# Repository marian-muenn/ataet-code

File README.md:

# Dokumentation des Projektes

## Projektrstruktur

- `./src`
  - beinhaltet den Quellcode
- `./boards`
  - beinhaltet die Devicetree overlays
- `./prj.conf`
  - beinhaltet die Kernel-Konfiguration
- `./doc`
  - beinhaltet die Dokumtation des C Codes
- `./west`
  - beinhaltet Metadaten für das Build Tool
- `./kicad`
  - beinhaltet das Kicad-Projekt zur Platine

## Installation der benötigten Tool

Zur Installation der Tools unter Linux liegen 3 Skripte bei,
die sukzessive ausgeführt werden müssen.

- `./install-zephyr-sdk.sh`
  - Installiert das Zephyr SDK
- `./create-venv.sh`
  - Richtet eine virtuelle Python Umgebung mit dem von Zephyr
  genutzten build Tool "west" ein
- `./west_init.sh`
  - Initialisiert den West workspace

Alternativ kann auch der
  [offizielle Installationsguide](https://docs.zephyrproject.org/latest/develop/getting_started/index.html)
  genutzt werden.

- Außerdem werden Cmake, Python und Python-venv benötigt.

## Eintragen der Passwörter

- Aus Sicherheitsgründen sind die Benutzerpasswörter für MQTT entfernt worden.
- Diese müssen in den Dateien src/mm_config.h und mqtt-py/mqtt.py eintgetragen werden.

## Kompilieren und installieren der Firmware

- Das STM Nucleo-F756zg entwicklunsboard muss mit dem PC über USB erbunden werden.
- Mit `source .venv/bin/activate` wird die Python Umgebung mit den build tools eingebunden.
- Mit `west build -b nucleo_f756zg -p` wird der Programmcode für ein Board mit LTE-Modem kompiliert
- Mit `west build -b nucleo_f756zg -p -D -- -DOVERLAY_CONF=wifi.conf` wird der Programmcode für die Platine mit WLAN Modul kompiliert
- Anschließend kann das Programm mit `west flash` auf den
  Microcontroller übertragen werden

## Konsolenlog und Debugging

- mit `picocom /dev/ttyACM0 --baud=115200` wird der Konsolenoutput des
  Microcontrollers angezeigt.
- Mit `west debug` kann außerdem eine gdb Sitzung zum Debugging gestartet werden.

## Empfangen der Fotos über MQTT

- In mqtt-py liegt ein kleines Python tool, das es ermöglicht die Bilder
  über den MQTT Sever zu empfangen.
- Dieses lässt sich mit `python mqtt-py/mqtt.py` ausführen.
- Anschließend meldet sich das Tool am MQTT-Server an und speichert das
  neuste .jpeg in den lokalen ordner.

## Erstellen der Codedokumentation

- Mit dem tool `doxygen` kann die Dokumentation erstellt werden
- Diese liegt dann im Verzeichnis ./doc in den Dateiformaten .html und als Latex-Dokument

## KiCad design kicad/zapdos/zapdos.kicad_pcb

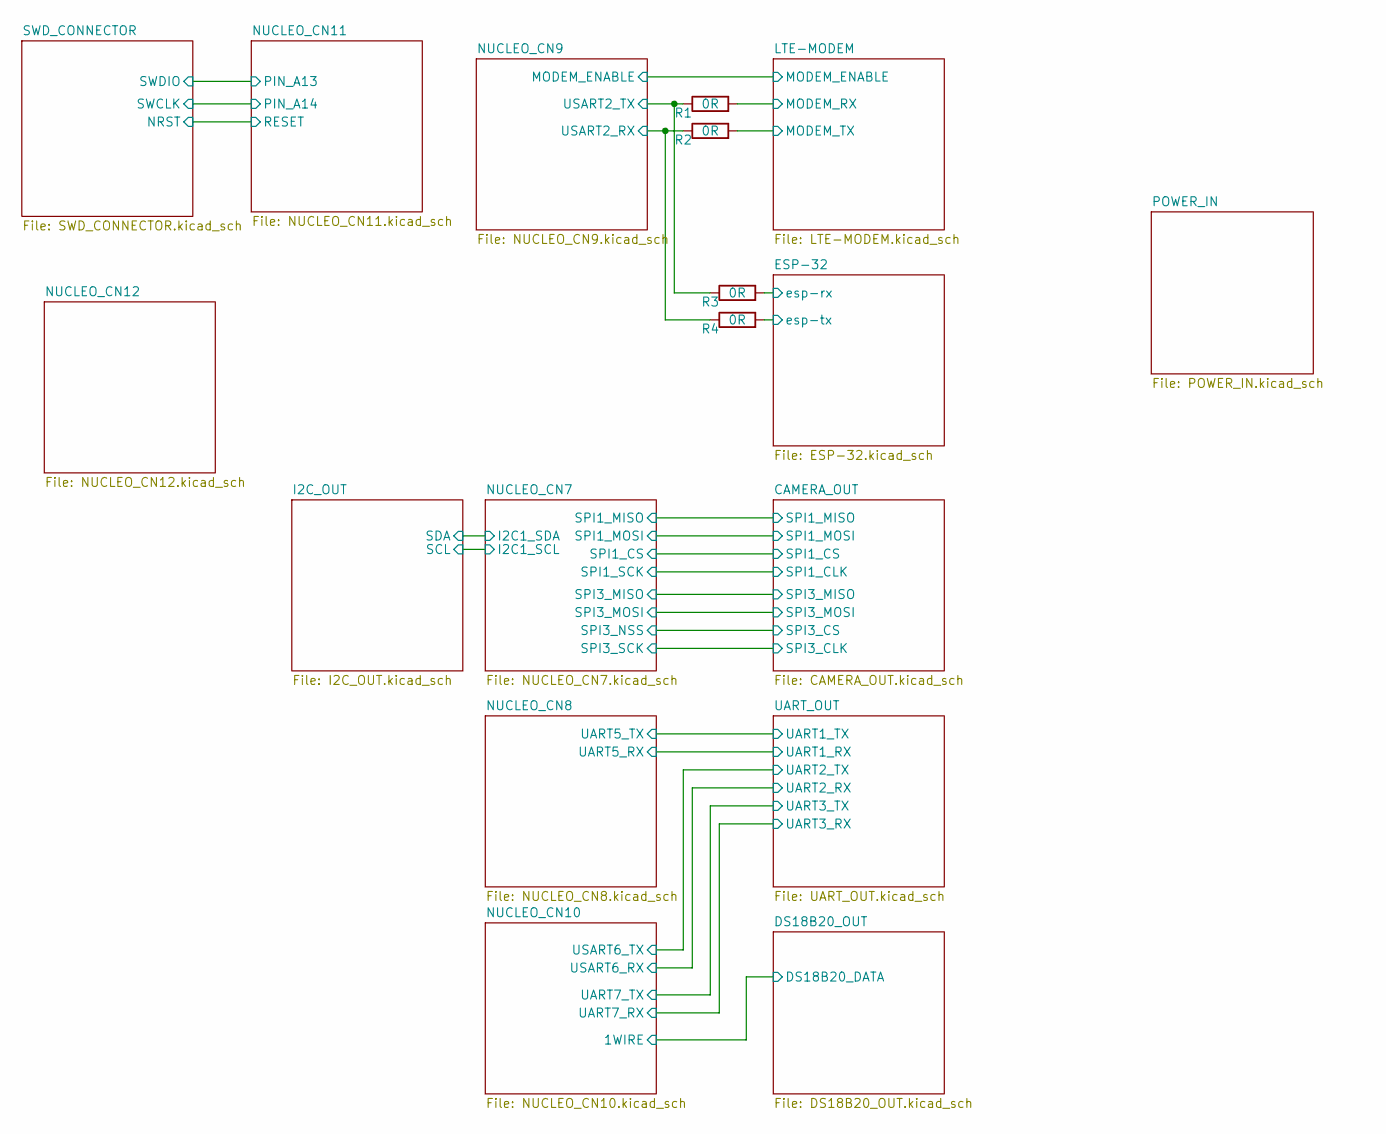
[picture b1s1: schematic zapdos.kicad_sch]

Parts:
R1, R2, R3, R4: 0R; R_0805_2012Metric_Pad1.20x1.40mm_HandSolder

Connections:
/ESP-32/esp-rx: R3.2; also elsewhere on the board
/ESP-32/esp-tx: R4.2; also elsewhere on the board
/LTE-MODEM/MODEM_RX: R1.2; also elsewhere on the board
/LTE-MODEM/MODEM_TX: R2.2; also elsewhere on the board
/NUCLEO_CN9/USART2_RX: R2.1, R4.1; also elsewhere on the board
/NUCLEO_CN9/USART2_TX: R1.1, R3.1; also elsewhere on the board

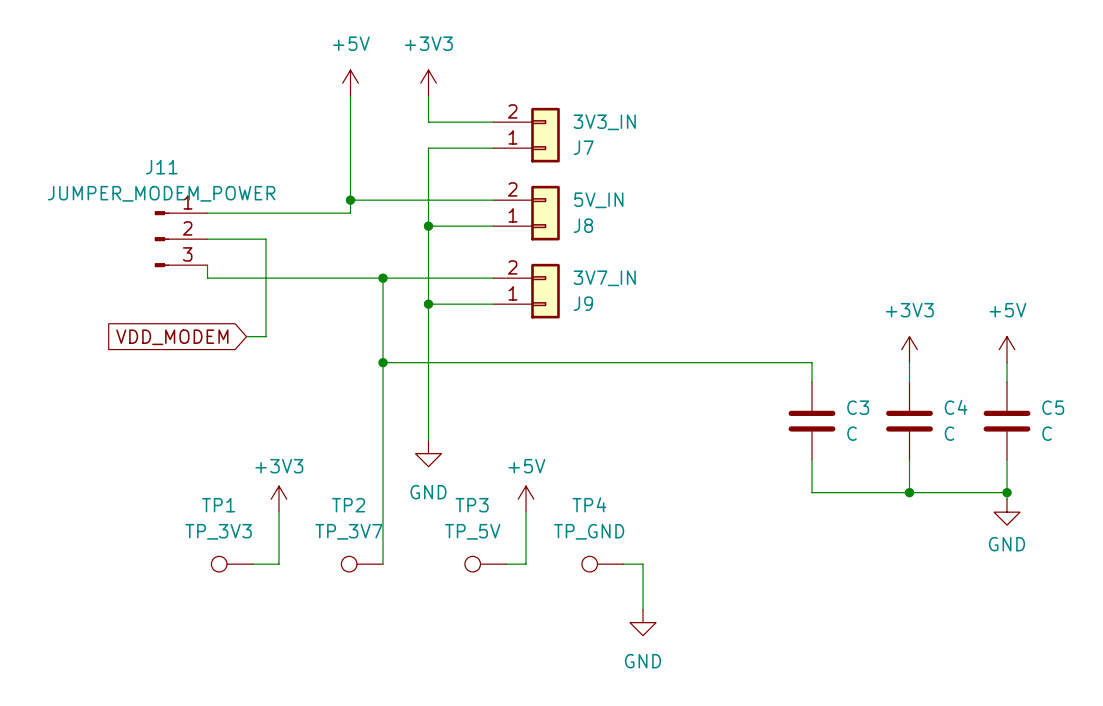
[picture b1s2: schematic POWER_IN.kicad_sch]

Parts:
C3, C4, C5: C; C_1210_3225Metric_Pad1.33x2.70mm_HandSolder
J7: 3V3_IN; JST_PH_B2B-PH-K_1x02_P2.00mm_Vertical
J8: 5V_IN; JST_PH_B2B-PH-K_1x02_P2.00mm_Vertical
J9: 3V7_IN; JST_PH_B2B-PH-K_1x02_P2.00mm_Vertical
J11: JUMPER_MODEM_POWER; PinHeader_1x03_P2.54mm_Vertical
TP1: TP_3V3; TestPoint_Pad_2.5x2.5mm
TP2: TP_3V7; TestPoint_Pad_2.5x2.5mm
TP3: TP_5V; TestPoint_Pad_2.5x2.5mm
TP4: TP_GND; TestPoint_Pad_2.5x2.5mm

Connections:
+3V3: C4.1, J7.2, TP1.1; also elsewhere on the board
+5V: C5.1, J8.2, J11.1, TP3.1; also elsewhere on the board
GND: C3.2, C4.2, C5.2, J7.1, J8.1, J9.1, TP4.1; also elsewhere on the board
unnamed: C3.1, J9.2, J11.3, TP2.1
VDD_MODEM: J11.2; also elsewhere on the board

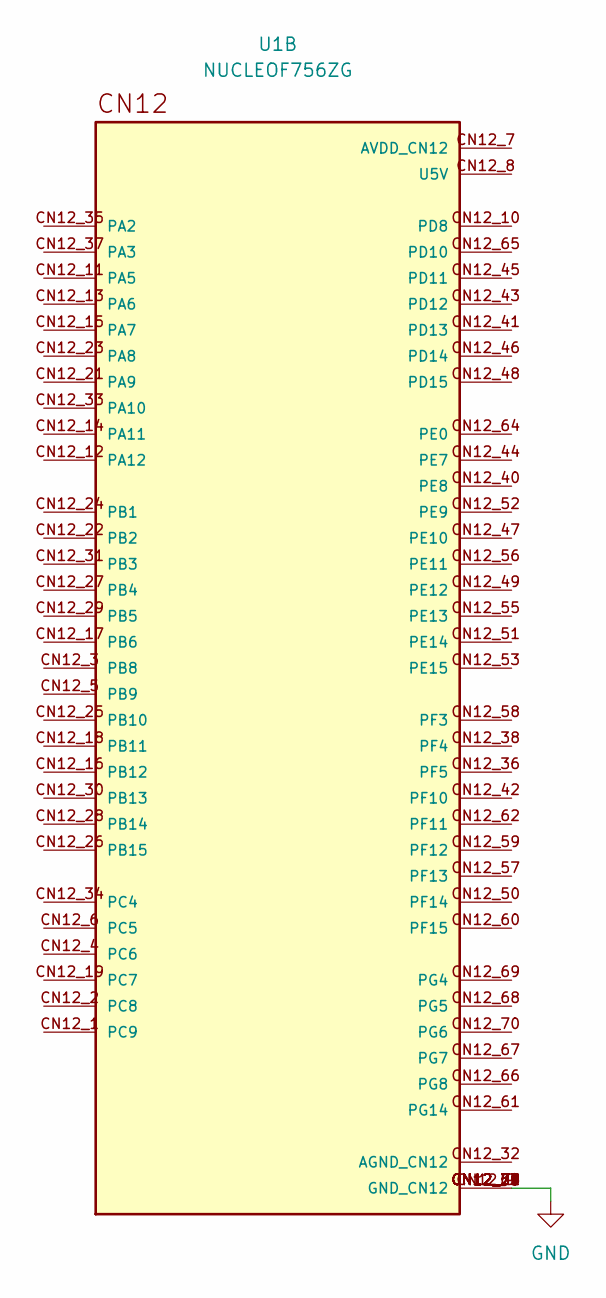
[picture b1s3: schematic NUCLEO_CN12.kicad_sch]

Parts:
U1: NUCLEOF756ZG; MODULE_NUCLEOF756ZG; PARTREV 9

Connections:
GND: U1.CN12_9 (GND_CN12), U1.CN12_20 (GND_CN12), U1.CN12_39 (GND_CN12), U1.CN12_54 (GND_CN12), U1.CN12_63 (GND_CN12), U1.CN12_71 (GND_CN12), U1.CN12_72 (GND_CN12); also elsewhere on the board

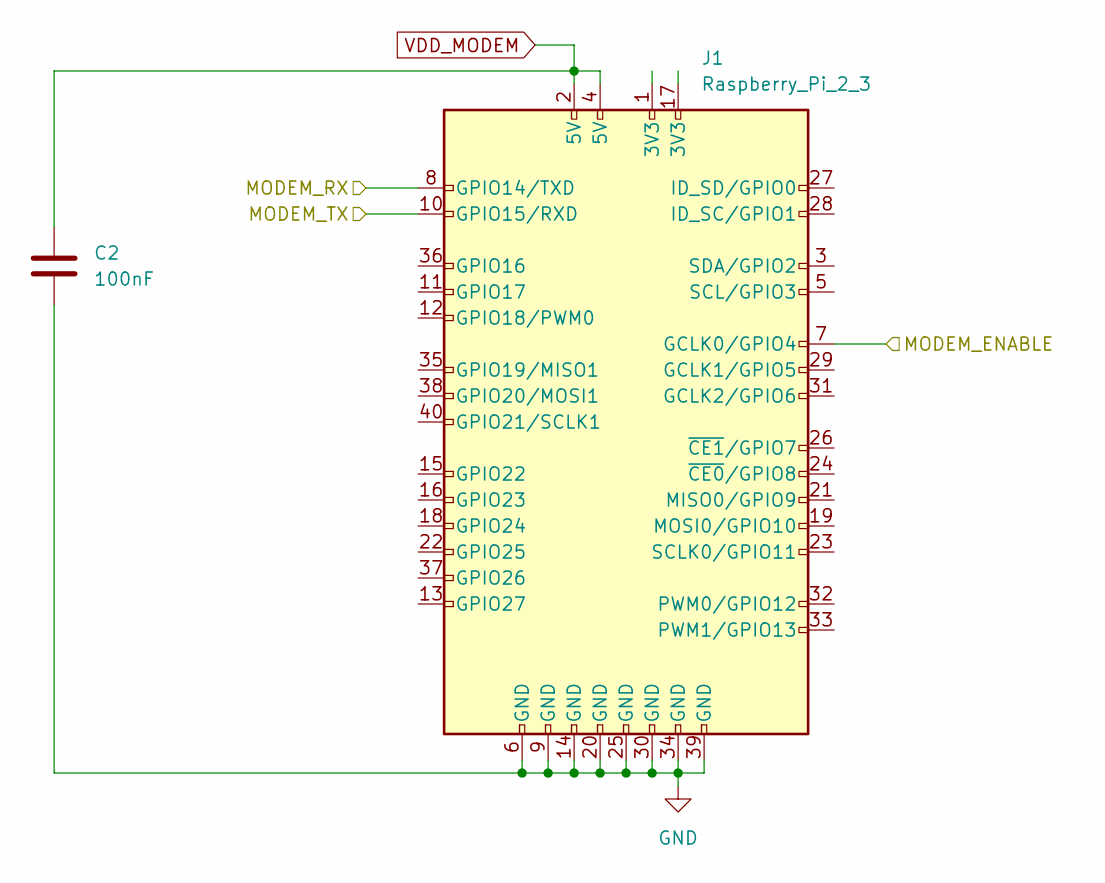
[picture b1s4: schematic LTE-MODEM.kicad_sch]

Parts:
C2: 100nF; C_1210_3225Metric_Pad1.33x2.70mm_HandSolder
J1: Raspberry_Pi_2_3; PI_ZERO_HAT

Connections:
/LTE-MODEM/MODEM_ENABLE: J1.7 (GCLK0/GPIO4); also elsewhere on the board
/LTE-MODEM/MODEM_RX: J1.8 (GPIO14/TXD); also elsewhere on the board
/LTE-MODEM/MODEM_TX: J1.10 (GPIO15/RXD); also elsewhere on the board
GND: C2.2, J1.6 (GND), J1.9 (GND), J1.14 (GND), J1.20 (GND), J1.25 (GND), J1.30 (GND), J1.34 (GND), J1.39 (GND); also elsewhere on the board
VDD_MODEM: C2.1, J1.2 (5V), J1.4 (5V); also elsewhere on the board

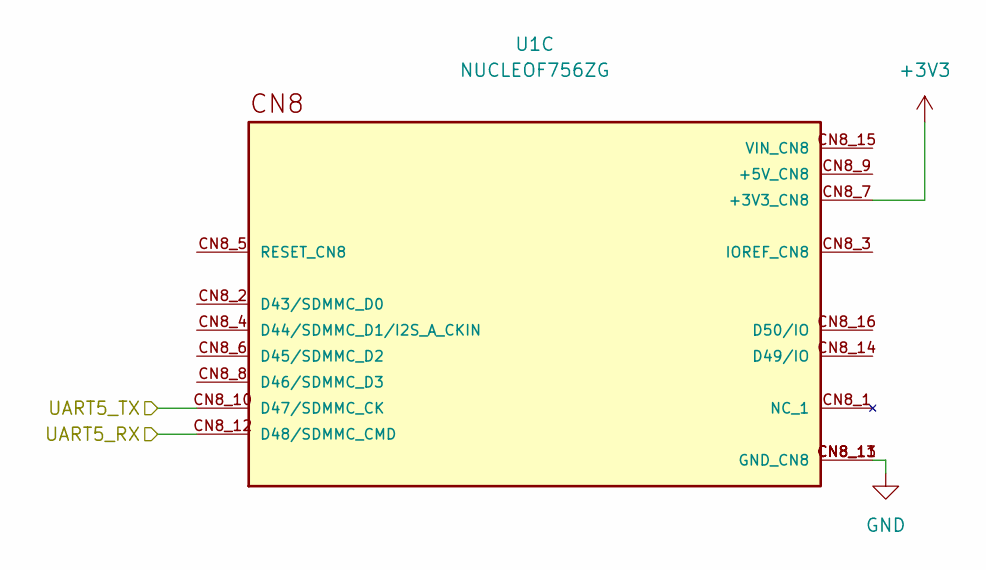
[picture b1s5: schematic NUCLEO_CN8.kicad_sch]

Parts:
U1: NUCLEOF756ZG; MODULE_NUCLEOF756ZG; PARTREV 9

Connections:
+3V3: U1.CN8_7 (+3V3_CN8); also elsewhere on the board
/NUCLEO_CN8/UART5_RX: U1.CN8_12 (D48/SDMMC_CMD); also elsewhere on the board
/NUCLEO_CN8/UART5_TX: U1.CN8_10 (D47/SDMMC_CK); also elsewhere on the board
GND: U1.CN8_11 (GND_CN8), U1.CN8_13 (GND_CN8); also elsewhere on the board

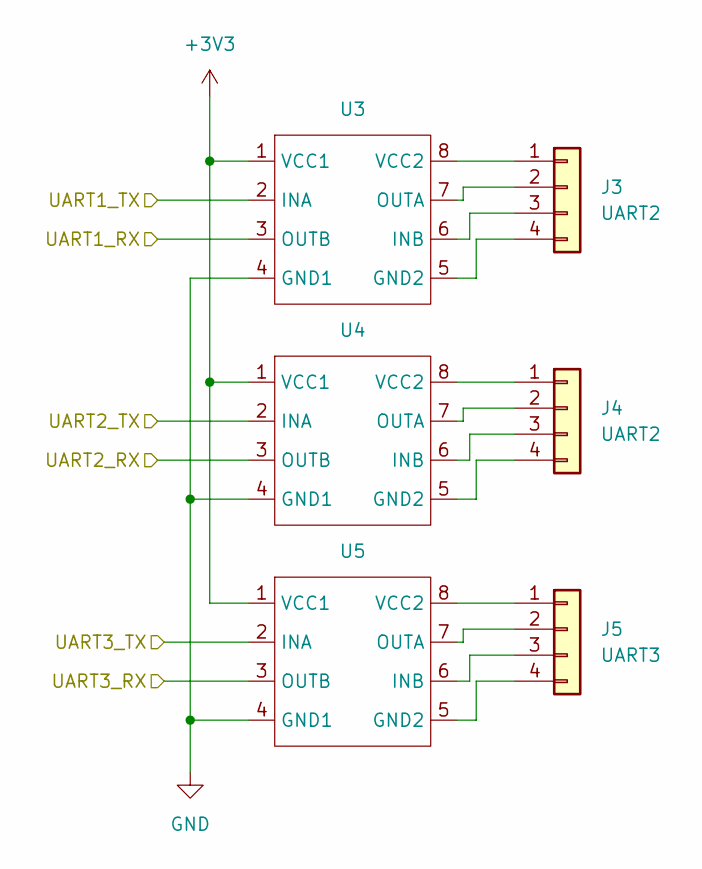
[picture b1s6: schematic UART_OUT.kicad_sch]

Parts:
J3, J4: UART2; JST_PH_B4B-PH-K_1x04_P2.00mm_Vertical
J5: UART3; JST_PH_B4B-PH-K_1x04_P2.00mm_Vertical
U3, U4, U5: SOIC-8_3.9x4.9mm_P1.27mm

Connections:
+3V3: U3.1 (VCC1), U4.1 (VCC1), U5.1 (VCC1); also elsewhere on the board
/NUCLEO_CN8/UART5_RX: U3.3 (OUTB); also elsewhere on the board
/NUCLEO_CN8/UART5_TX: U3.2 (INA); also elsewhere on the board
/NUCLEO_CN10/UART7_RX: U5.3 (OUTB); also elsewhere on the board
/NUCLEO_CN10/UART7_TX: U5.2 (INA); also elsewhere on the board
/NUCLEO_CN10/USART6_RX: U4.3 (OUTB); also elsewhere on the board
/NUCLEO_CN10/USART6_TX: U4.2 (INA); also elsewhere on the board
GND: U3.4 (GND1), U4.4 (GND1), U5.4 (GND1); also elsewhere on the board
unnamed: J3.1, U3.8 (VCC2)
unnamed: J3.2, U3.7 (OUTA)
unnamed: J3.3, U3.6 (INB)
unnamed: J3.4, U3.5 (GND2)
unnamed: J4.1, U4.8 (VCC2)
unnamed: J4.2, U4.7 (OUTA)
unnamed: J4.3, U4.6 (INB)
unnamed: J4.4, U4.5 (GND2)
unnamed: J5.1, U5.8 (VCC2)
unnamed: J5.2, U5.7 (OUTA)
unnamed: J5.3, U5.6 (INB)
unnamed: J5.4, U5.5 (GND2)

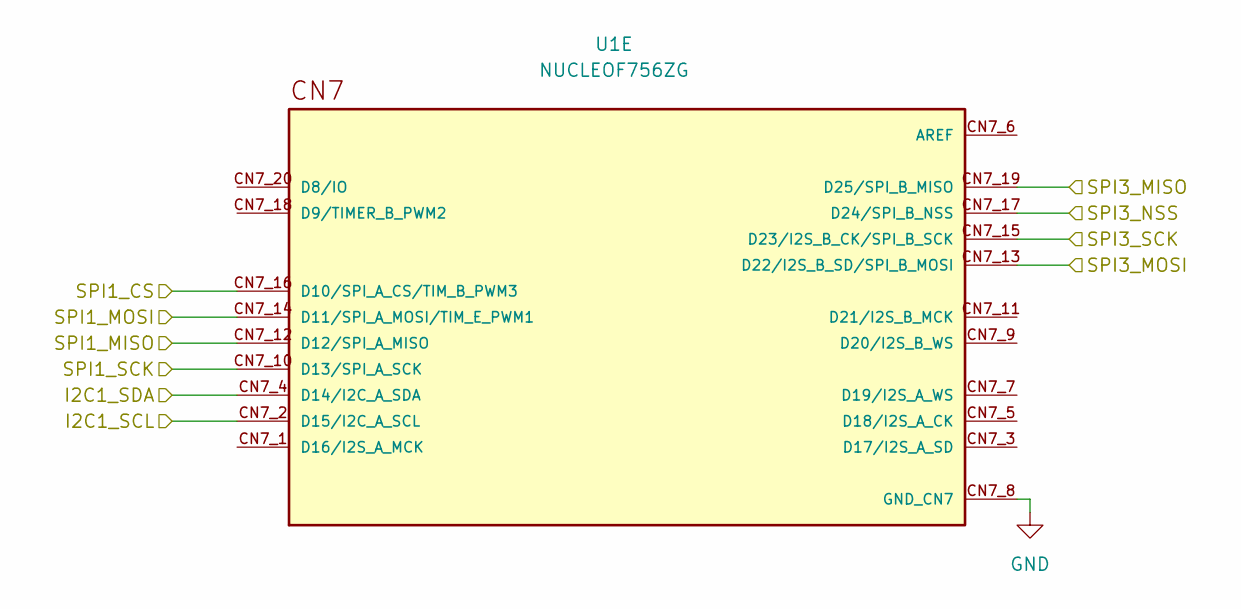
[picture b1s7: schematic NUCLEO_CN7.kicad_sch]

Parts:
U1: NUCLEOF756ZG; MODULE_NUCLEOF756ZG; PARTREV 9

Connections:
/CAMERA_OUT/SPI1_CLK: U1.CN7_10 (D13/SPI_A_SCK); also elsewhere on the board
/CAMERA_OUT/SPI1_CS: U1.CN7_16 (D10/SPI_A_CS/TIM_B_PWM3); also elsewhere on the board
/CAMERA_OUT/SPI1_MISO: U1.CN7_12 (D12/SPI_A_MISO); also elsewhere on the board
/CAMERA_OUT/SPI1_MOSI: U1.CN7_14 (D11/SPI_A_MOSI/TIM_E_PWM1); also elsewhere on the board
/CAMERA_OUT/SPI3_CLK: U1.CN7_15 (D23/I2S_B_CK/SPI_B_SCK); also elsewhere on the board
/CAMERA_OUT/SPI3_CS: U1.CN7_17 (D24/SPI_B_NSS); also elsewhere on the board
/CAMERA_OUT/SPI3_MISO: U1.CN7_19 (D25/SPI_B_MISO); also elsewhere on the board
/CAMERA_OUT/SPI3_MOSI: U1.CN7_13 (D22/I2S_B_SD/SPI_B_MOSI); also elsewhere on the board
/I2C_OUT/SCL: U1.CN7_2 (D15/I2C_A_SCL); also elsewhere on the board
/I2C_OUT/SDA: U1.CN7_4 (D14/I2C_A_SDA); also elsewhere on the board
GND: U1.CN7_8 (GND_CN7); also elsewhere on the board

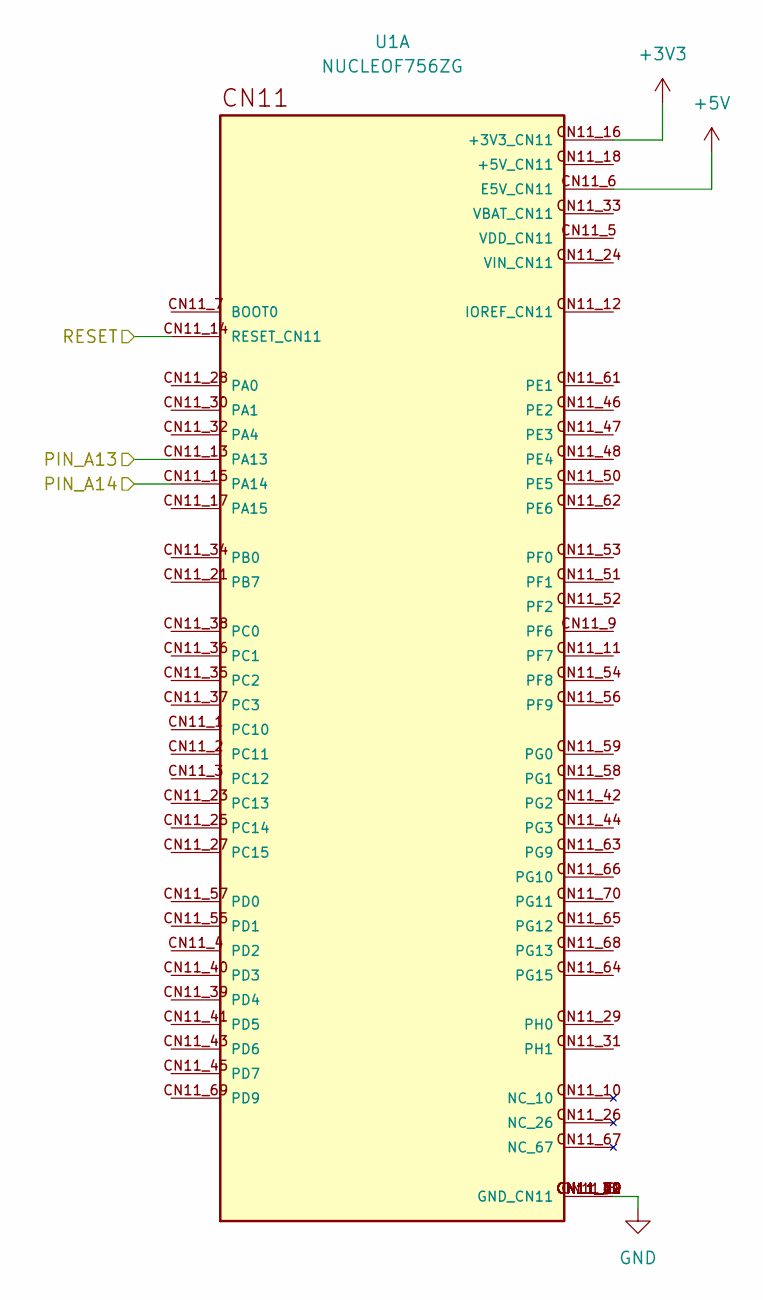
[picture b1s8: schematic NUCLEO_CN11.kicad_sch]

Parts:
U1: NUCLEOF756ZG; MODULE_NUCLEOF756ZG; PARTREV 9

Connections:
+3V3: U1.CN11_16 (+3V3_CN11); also elsewhere on the board
+5V: U1.CN11_6 (E5V_CN11); also elsewhere on the board
/NUCLEO_CN11/PIN_A13: U1.CN11_13 (PA13); also elsewhere on the board
/NUCLEO_CN11/PIN_A14: U1.CN11_15 (PA14); also elsewhere on the board
/NUCLEO_CN11/RESET: U1.CN11_14 (RESET_CN11); also elsewhere on the board
GND: U1.CN11_8 (GND_CN11), U1.CN11_19 (GND_CN11), U1.CN11_20 (GND_CN11), U1.CN11_22 (GND_CN11), U1.CN11_49 (GND_CN11), U1.CN11_60 (GND_CN11), U1.CN11_71 (GND_CN11), U1.CN11_72 (GND_CN11); also elsewhere on the board

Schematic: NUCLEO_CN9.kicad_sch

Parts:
U1: NUCLEOF756ZG; MODULE_NUCLEOF756ZG; PARTREV 9

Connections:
/LTE-MODEM/MODEM_ENABLE: U1.CN9_2 (D51/USART_B_SCLK); also elsewhere on the board
/NUCLEO_CN9/USART2_RX: U1.CN9_4 (D52/USART_B_RX); also elsewhere on the board
/NUCLEO_CN9/USART2_TX: U1.CN9_6 (D53/USART_B_TX); also elsewhere on the board
GND: U1.CN9_12 (GND_CN9), U1.CN9_23 (GND_CN9); also elsewhere on the board

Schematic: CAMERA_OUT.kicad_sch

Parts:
J2: SPI1; JST_PH_B6B-PH-K_1x06_P2.00mm_Vertical
J12: SPI3; JST_PH_B6B-PH-K_1x06_P2.00mm_Vertical

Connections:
+3V3: J2.1, J12.1; also elsewhere on the board
/CAMERA_OUT/SPI1_CLK: J2.3; also elsewhere on the board
/CAMERA_OUT/SPI1_CS: J2.6; also elsewhere on the board
/CAMERA_OUT/SPI1_MISO: J2.4; also elsewhere on the board
/CAMERA_OUT/SPI1_MOSI: J2.5; also elsewhere on the board
/CAMERA_OUT/SPI3_CLK: J12.3; also elsewhere on the board
/CAMERA_OUT/SPI3_CS: J12.6; also elsewhere on the board
/CAMERA_OUT/SPI3_MISO: J12.4; also elsewhere on the board
/CAMERA_OUT/SPI3_MOSI: J12.5; also elsewhere on the board
GND: J2.2, J12.2; also elsewhere on the board

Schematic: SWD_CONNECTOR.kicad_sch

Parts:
J10: SWD; PinHeader_1x06_P2.54mm_Vertical

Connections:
+3V3: J10.1; also elsewhere on the board
/NUCLEO_CN11/PIN_A13: J10.4; also elsewhere on the board
/NUCLEO_CN11/PIN_A14: J10.2; also elsewhere on the board
/NUCLEO_CN11/RESET: J10.5; also elsewhere on the board
GND: J10.3; also elsewhere on the board

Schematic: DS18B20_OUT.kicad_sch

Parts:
J6: DS18B20; JST_PH_B3B-PH-K_1x03_P2.00mm_Vertical
R5: 10K; R_0805_2012Metric_Pad1.20x1.40mm_HandSolder

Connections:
+3V3: J6.1, R5.1; also elsewhere on the board
/DS18B20_OUT/DS18B20_DATA: J6.2, R5.2; also elsewhere on the board
GND: J6.3; also elsewhere on the board

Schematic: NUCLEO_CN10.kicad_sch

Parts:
U1: NUCLEOF756ZG; MODULE_NUCLEOF756ZG; PARTREV 9

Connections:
/DS18B20_OUT/DS18B20_DATA: U1.CN10_2 (D7/IO); also elsewhere on the board
/NUCLEO_CN10/UART7_RX: U1.CN10_18 (D42/TIMER_A_PWM1N); also elsewhere on the board
/NUCLEO_CN10/UART7_TX: U1.CN10_20 (D41/TIMER_A_ETR); also elsewhere on the board
/NUCLEO_CN10/USART6_RX: U1.CN10_16 (D0/USART_A_RX); also elsewhere on the board
/NUCLEO_CN10/USART6_TX: U1.CN10_14 (D1/USART_A_TX); also elsewhere on the board
GND: U1.CN10_5 (GND_CN10), U1.CN10_17 (GND_CN10), U1.CN10_22 (GND_CN10), U1.CN10_27 (GND_CN10); also elsewhere on the board

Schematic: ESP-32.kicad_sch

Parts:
C1: 100nF; C_1210_3225Metric_Pad1.33x2.70mm_HandSolder
U2: ESP32-DEVKITC; MODULE_ESP32-DEVKITC; PARTREV N/A

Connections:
+3V3: C1.1, U2.1 (3V3); also elsewhere on the board
/ESP-32/esp-rx: U2.27 (IO16); also elsewhere on the board
/ESP-32/esp-tx: U2.28 (IO17); also elsewhere on the board
GND: C1.2, U2.14 (GND1), U2.32 (GND2), U2.38 (GND3); also elsewhere on the board

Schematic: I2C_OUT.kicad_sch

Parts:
J13: Conn_01x04; JST_PH_B4B-PH-K_1x04_P2.00mm_Vertical

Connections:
+3V3: J13.1; also elsewhere on the board
/I2C_OUT/SCL: J13.2; also elsewhere on the board
/I2C_OUT/SDA: J13.3; also elsewhere on the board
GND: J13.4; also elsewhere on the board

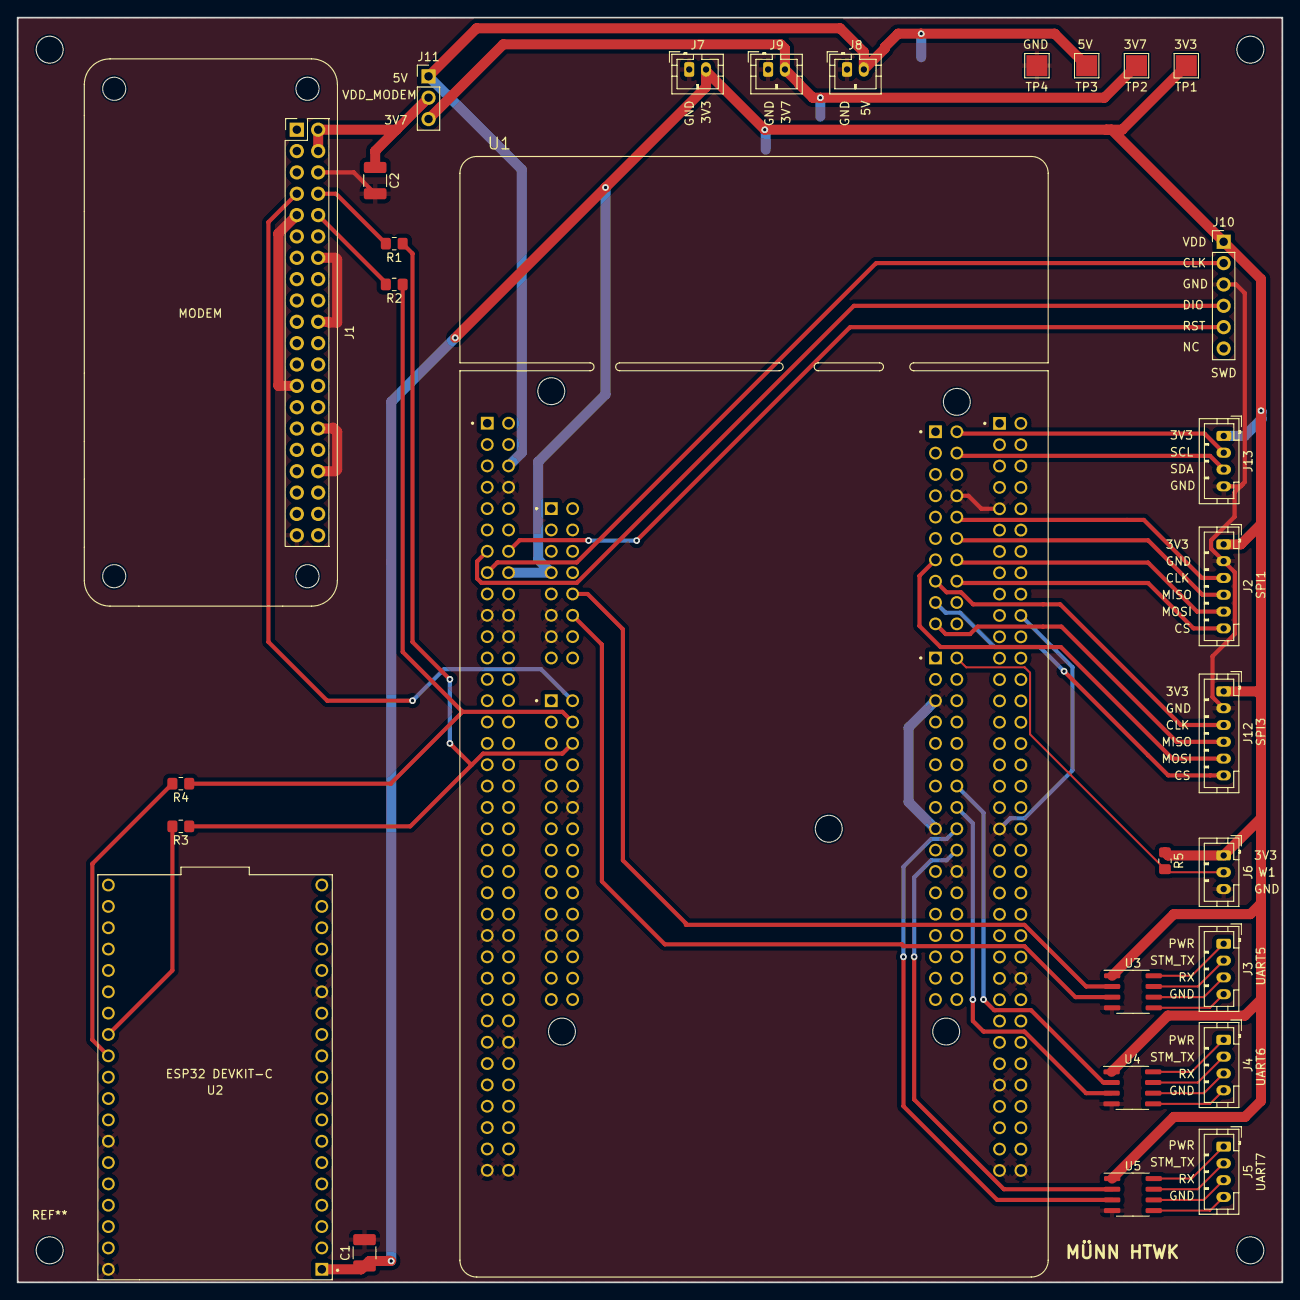
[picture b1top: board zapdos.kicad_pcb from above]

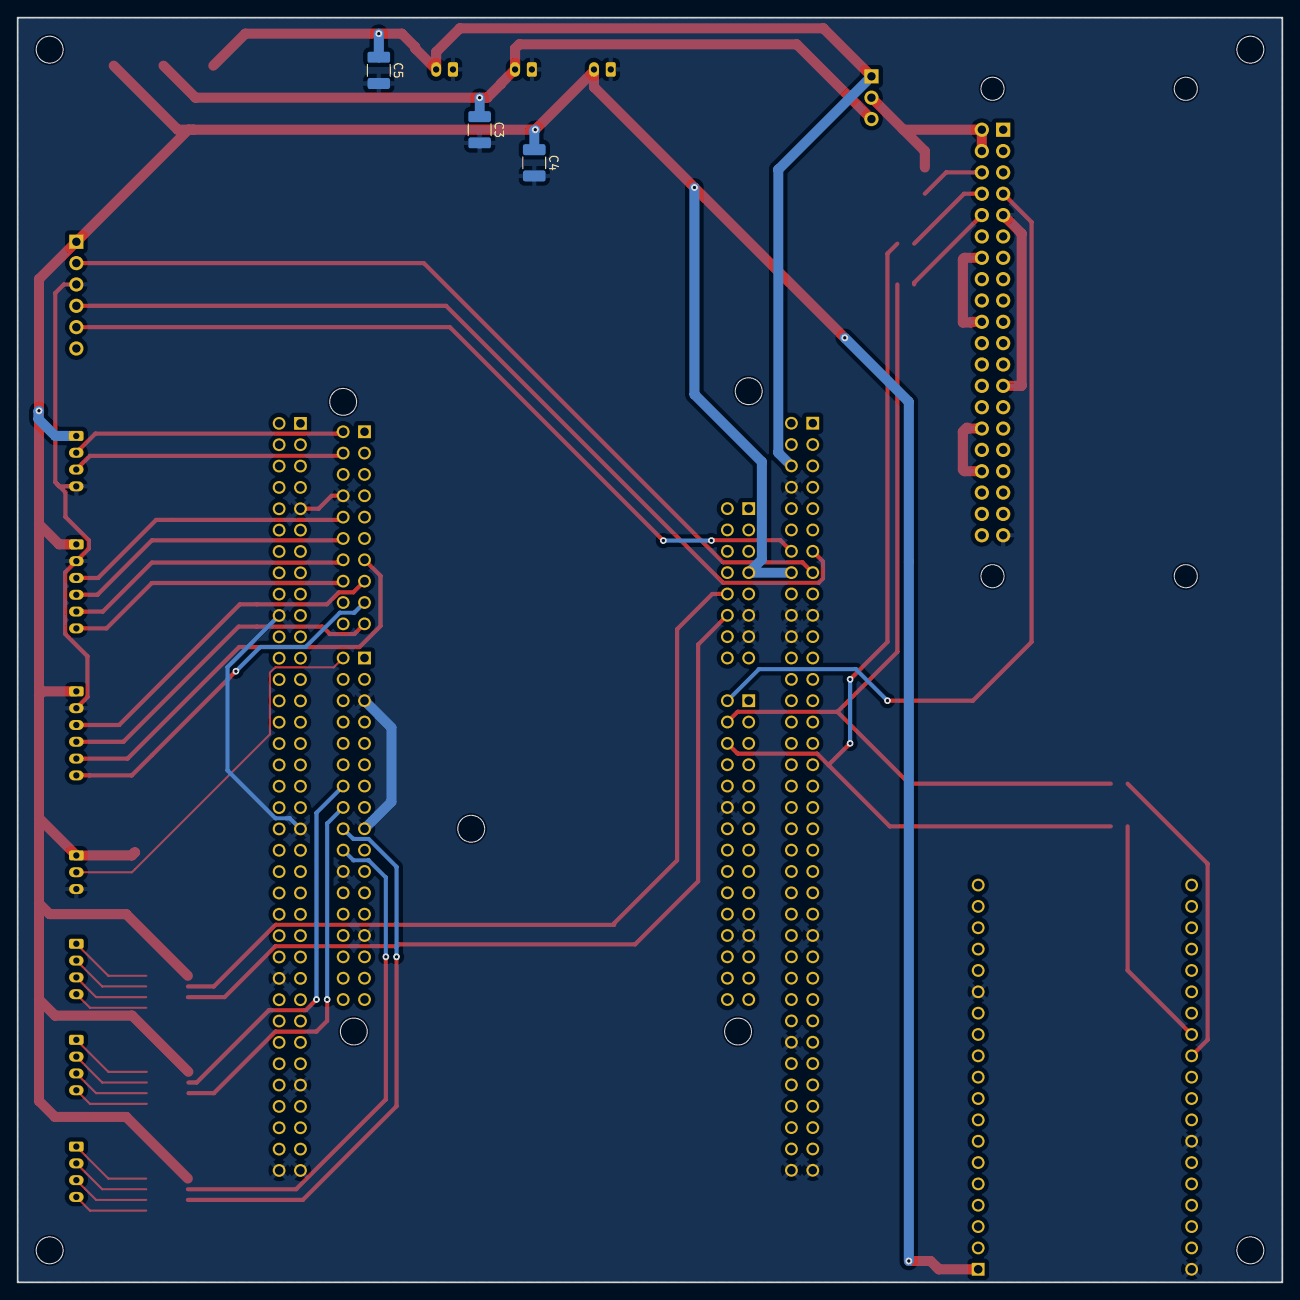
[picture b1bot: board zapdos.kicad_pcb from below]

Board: 2 copper layers, 150.5 x 150.5 mm, 32 parts (3 on the bottom side), 44 nets.

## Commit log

2024-03-17 code
2024-03-17 added kicad, gitignore
